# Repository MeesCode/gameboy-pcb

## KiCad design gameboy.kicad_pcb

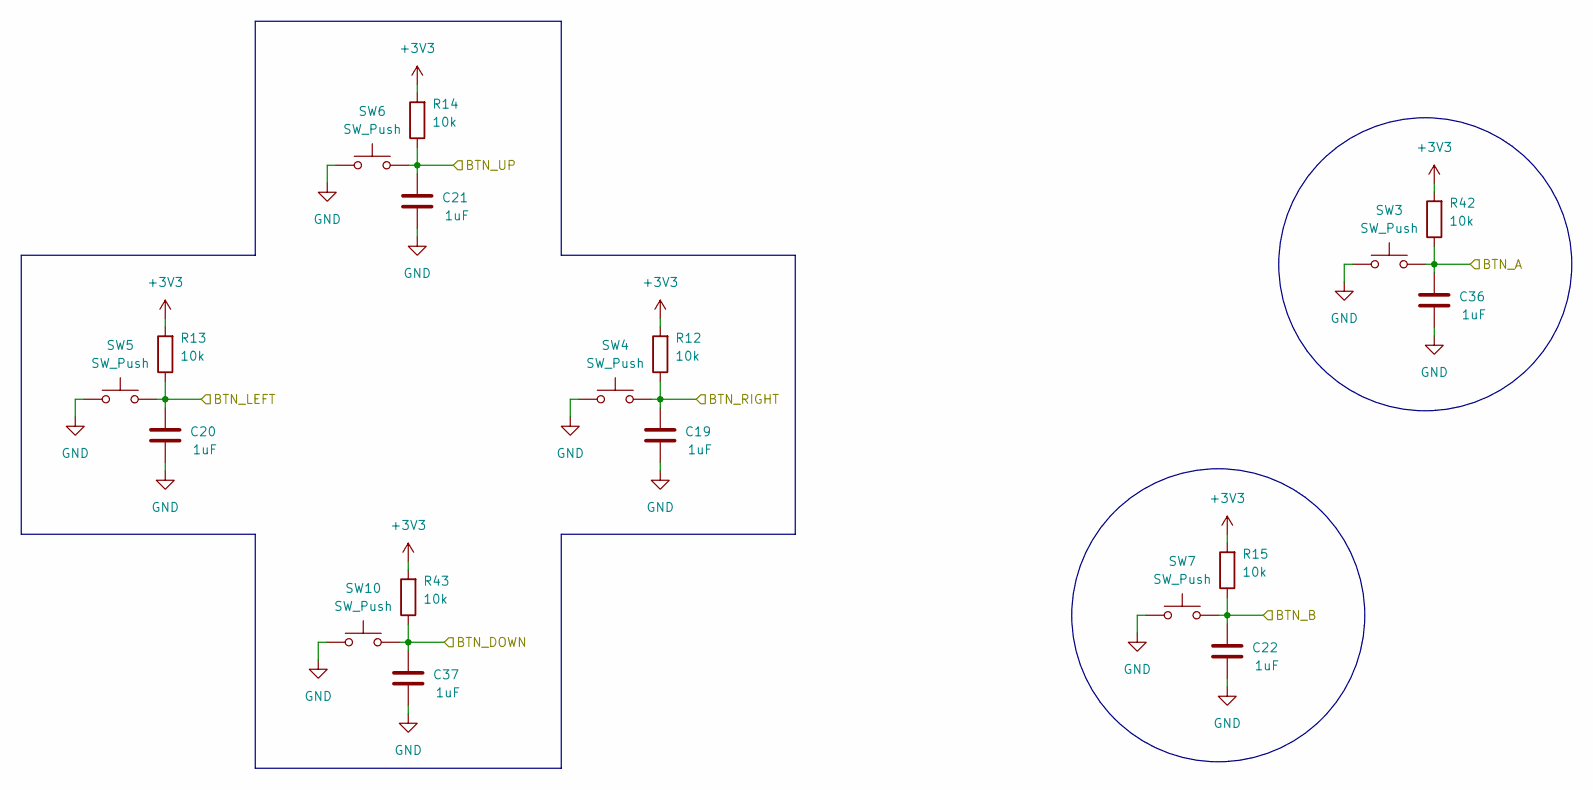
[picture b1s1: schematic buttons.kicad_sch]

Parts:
C19, C20, C21, C22, C36, C37: 1uF; C_0402_1005Metric; Manufacturer Part Number CL05A105KA5NQNC; LCSC C52923
R12, R13, R14, R15, R42, R43: 10k; R_0603_1608Metric
SW3, SW4, SW5, SW6, SW7, SW10: SW_Push; SW_Push_1TS009xxxx-xxxx-xxxx_6x6x5mm; Manufacturer Part Number HX TS665WS 200gf; LCSC C5143657

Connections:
+3V3: R12.2, R13.2, R14.2, R15.2, R42.2, R43.2; also elsewhere on the board
/Buttons/BTN_A: C36.2, R42.1, SW3.2; also elsewhere on the board
/Buttons/BTN_B: C22.2, R15.1, SW7.2; also elsewhere on the board
/Buttons/BTN_DOWN: C37.2, R43.1, SW10.2; also elsewhere on the board
/Buttons/BTN_LEFT: C20.2, R13.1, SW5.2; also elsewhere on the board
/Buttons/BTN_RIGHT: C19.2, R12.1, SW4.2; also elsewhere on the board
/Buttons/BTN_UP: C21.2, R14.1, SW6.2; also elsewhere on the board
GND: C19.1, C20.1, C21.1, C22.1, C36.1, C37.1, SW3.1, SW4.1, SW5.1, SW6.1, SW7.1, SW10.1; also elsewhere on the board

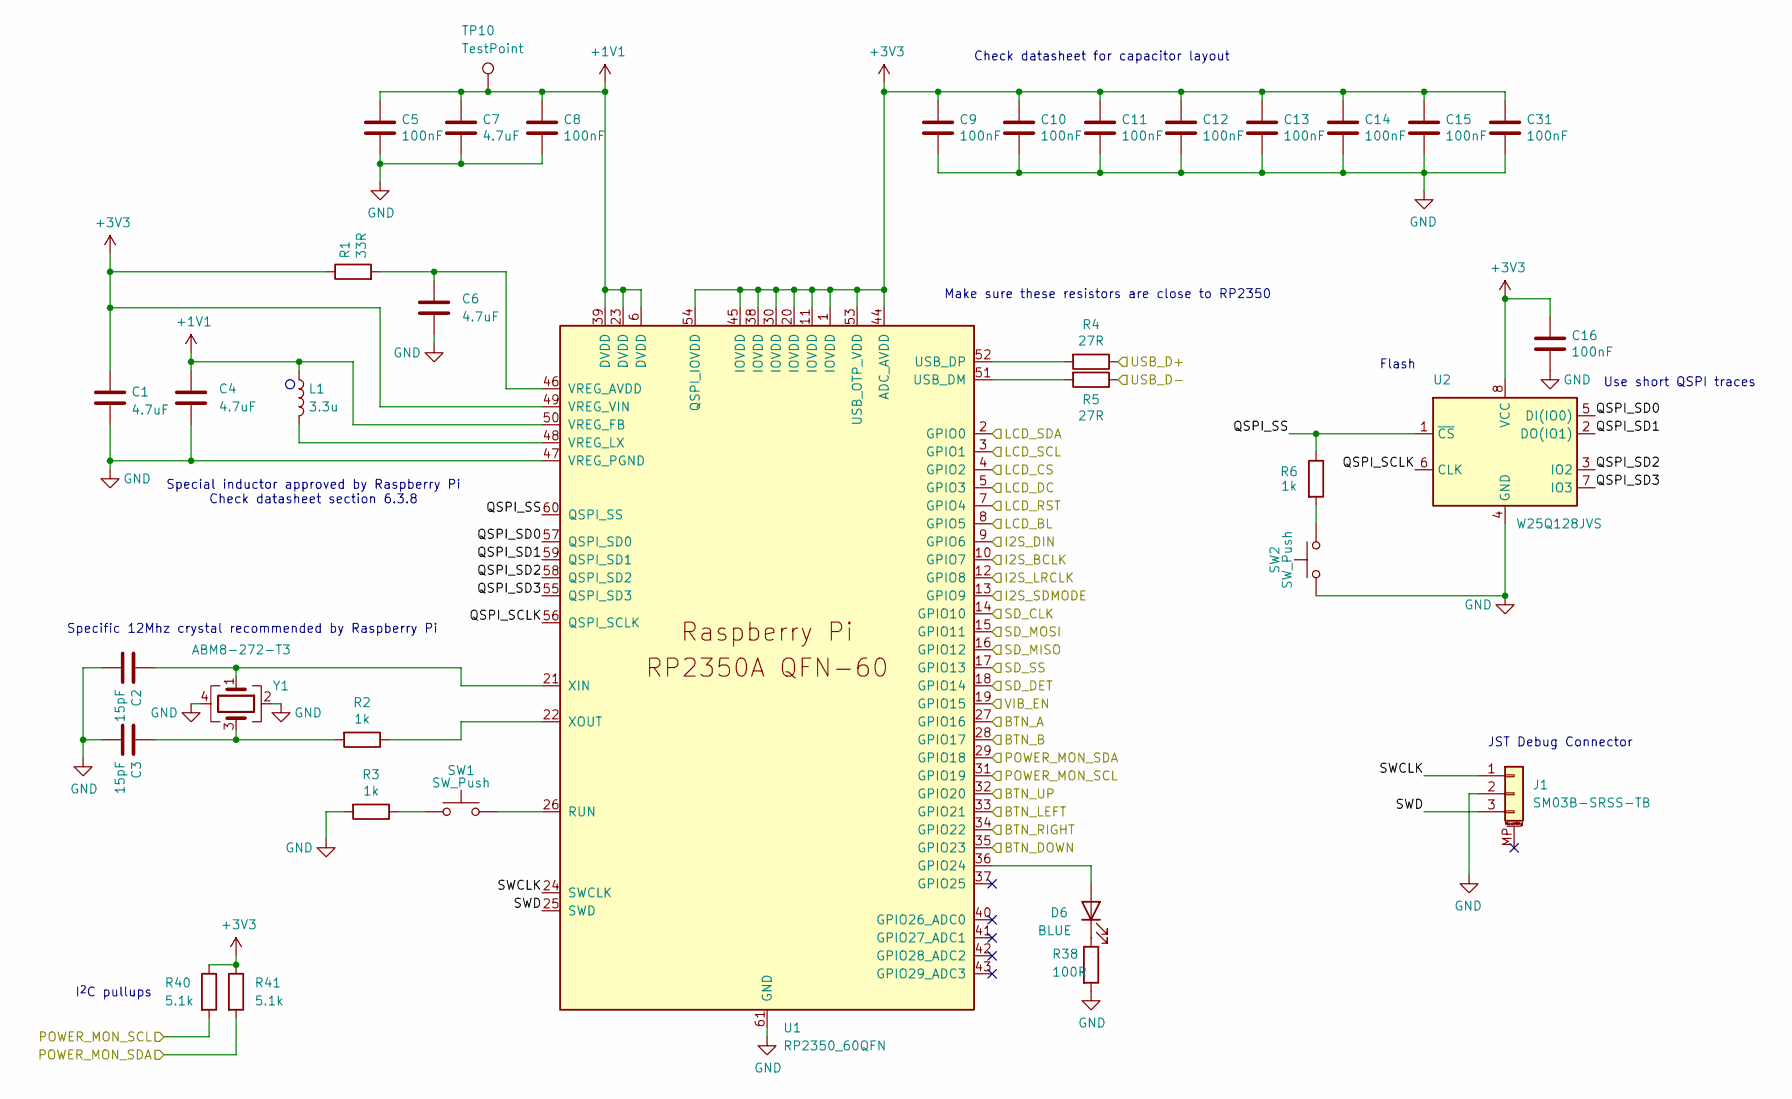
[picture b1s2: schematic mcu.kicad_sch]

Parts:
C1, C4, C6, C7: 4.7uF; C_0402_1005Metric
C2, C3: 15pF; C_0402_1005Metric
C5, C8, C9, C10, C11, C12, C13, C14, C15, C16, C31: 100nF; C_0402_1005Metric
D6: BLUE; LED_Sideways; Manufacturer Part Number XL-1606UBC; LCSC C965865
J1: SM03B-SRSS-TB; JST_SH_SM03B-SRSS-TB_1x03-1MP_P1.00mm_Horizontal; LCSC C160403
L1: 3.3u; L_pol_2016; Manufacturer Part Number AOTA-B201610S3R3-101-T; LCSC C42411119
R1: 33R; R_0402_1005Metric
R2, R3, R6: 1k; R_0603_1608Metric
R4, R5: 27R; R_0402_1005Metric
R38: 100R; R_0603_1608Metric; Manufacturer Part Number 0603WAF1000T5E; LCSC C22775
R40, R41: 5.1k; R_0603_1608Metric
SW1, SW2: SW_Push; SW_Push_1P1T_NO_Vertical_Wuerth_434133025816; Manufacturer Part Number 434133025816; LCSC C843674
TP10: TestPoint; TestPoint_Pad_D1.0mm
U1: RP2350_60QFN; RP2350-QFN-60-1EP_7x7_P0.4mm_EP3.4x3.4mm_ThermalVias; Manufacturer Part Number RP2350A; LCSC C42411118
U2: W25Q128JVS; SOIC-8_5.3x5.3mm_P1.27mm; Manufacturer Part Number W25Q128JVSIQ; LCSC C113767
Y1: ABM8-272-T3; Crystal_SMD_3225-4Pin_3.2x2.5mm; Manufacturer Part Number ABM8-272-T3; LCSC C20625731

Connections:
+1V1: C4.1, C5.1, C7.1, C8.1, L1.1, TP10.1 (1_1), U1.6 (DVDD), U1.23 (DVDD), U1.39 (DVDD), U1.50 (VREG_FB)
+3V3: C1.1, C9.1, C10.1, C11.1, C12.1, C13.1, C14.1, C15.1, C16.1, C31.1, R1.1, R40.1, R41.1, U1.1 (IOVDD), U1.11 (IOVDD), U1.20 (IOVDD), U1.30 (IOVDD), U1.38 (IOVDD), U1.44 (ADC_AVDD), U1.45 (IOVDD), U1.49 (VREG_VIN), U1.53 (USB_OTP_VDD), U1.54 (QSPI_IOVDD), U2.8 (VCC); also elsewhere on the board
/Audio/I2S_BCLK: U1.10 (GPIO7); also elsewhere on the board
/Audio/I2S_DIN: U1.9 (GPIO6); also elsewhere on the board
/Audio/I2S_LRCLK: U1.12 (GPIO8); also elsewhere on the board
/Audio/I2S_SDMODE: U1.13 (GPIO9); also elsewhere on the board
/Buttons/BTN_A: U1.27 (GPIO16); also elsewhere on the board
/Buttons/BTN_B: U1.28 (GPIO17); also elsewhere on the board
/Buttons/BTN_DOWN: U1.35 (GPIO23); also elsewhere on the board
/Buttons/BTN_LEFT: U1.33 (GPIO21); also elsewhere on the board
/Buttons/BTN_RIGHT: U1.34 (GPIO22); also elsewhere on the board
/Buttons/BTN_UP: U1.32 (GPIO20); also elsewhere on the board
/LCD/LCD_BL: U1.8 (GPIO5); also elsewhere on the board
/LCD/LCD_CS: U1.4 (GPIO2); also elsewhere on the board
/LCD/LCD_DC: U1.5 (GPIO3); also elsewhere on the board
/LCD/LCD_RST: U1.7 (GPIO4); also elsewhere on the board
/LCD/LCD_SCL: U1.3 (GPIO1); also elsewhere on the board
/LCD/LCD_SDA: U1.2 (GPIO0); also elsewhere on the board
/MCU/POWER_MON_SCL: R40.2, U1.31 (GPIO19); also elsewhere on the board
/MCU/POWER_MON_SDA: R41.2, U1.29 (GPIO18); also elsewhere on the board
/MCU/QSPI_SCLK: U1.56 (QSPI_SCLK), U2.6 (CLK)
/MCU/QSPI_SD0: U1.57 (QSPI_SD0), U2.5 (DI(IO0))
/MCU/QSPI_SD1: U1.59 (QSPI_SD1), U2.2 (DO(IO1))
/MCU/QSPI_SD2: U1.58 (QSPI_SD2), U2.3 (IO2)
/MCU/QSPI_SD3: U1.55 (QSPI_SD3), U2.7 (IO3)
/MCU/QSPI_SS: R6.1, U1.60 (QSPI_SS), U2.1 (~CS)
/MCU/SD_CLK: U1.14 (GPIO10); also elsewhere on the board
/MCU/SD_DET: U1.18 (GPIO14); also elsewhere on the board
/MCU/SD_MISO: U1.16 (GPIO12); also elsewhere on the board
/MCU/SD_MOSI: U1.15 (GPIO11); also elsewhere on the board
/MCU/SD_SS: U1.17 (GPIO13); also elsewhere on the board
/MCU/SWCLK: J1.1, U1.24 (SWCLK)
/MCU/SWD: J1.3, U1.25 (SWD)
/MCU/USB_D+: R4.1; also elsewhere on the board
/MCU/USB_D-: R5.1; also elsewhere on the board
/MCU/VIB_EN: U1.19 (GPIO15); also elsewhere on the board
GND: C1.2, C2.2, C3.2, C4.2, C5.2, C6.2, C7.2, C8.2, C9.2, C10.2, C11.2, C12.2, C13.2, C14.2, C15.2, C16.2, C31.2, J1.2, R3.2, R38.2, SW2.1, U1.47 (VREG_PGND), U1.61 (GND), U2.4 (GND), Y1.2, Y1.4; also elsewhere on the board
unnamed: C3.1, R2.2, Y1.3
unnamed: D6.2 (A), U1.36 (GPIO24)
unnamed: D6.1 (K), R38.1
unnamed: R3.1, SW1.1
unnamed: R6.2, SW2.2
unnamed: SW1.2, U1.26 (RUN)
unnamed: R5.2, U1.51 (USB_DM)
unnamed: R4.2, U1.52 (USB_DP)
unnamed: C6.1, R1.2, U1.46 (VREG_AVDD)
unnamed: L1.2, U1.48 (VREG_LX)
unnamed: C2.1, U1.21 (XIN), Y1.1
unnamed: R2.1, U1.22 (XOUT)

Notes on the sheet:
Check datasheet for capacitor layout
Special inductor approved by Raspberry Pi Check datasheet section 6.3.8
Specific 12Mhz crystal recommended by Raspberry Pi
Use short QSPI traces
Make sure these resistors are close to RP2350
Flash
I^{2}C pullups
JST Debug Connector

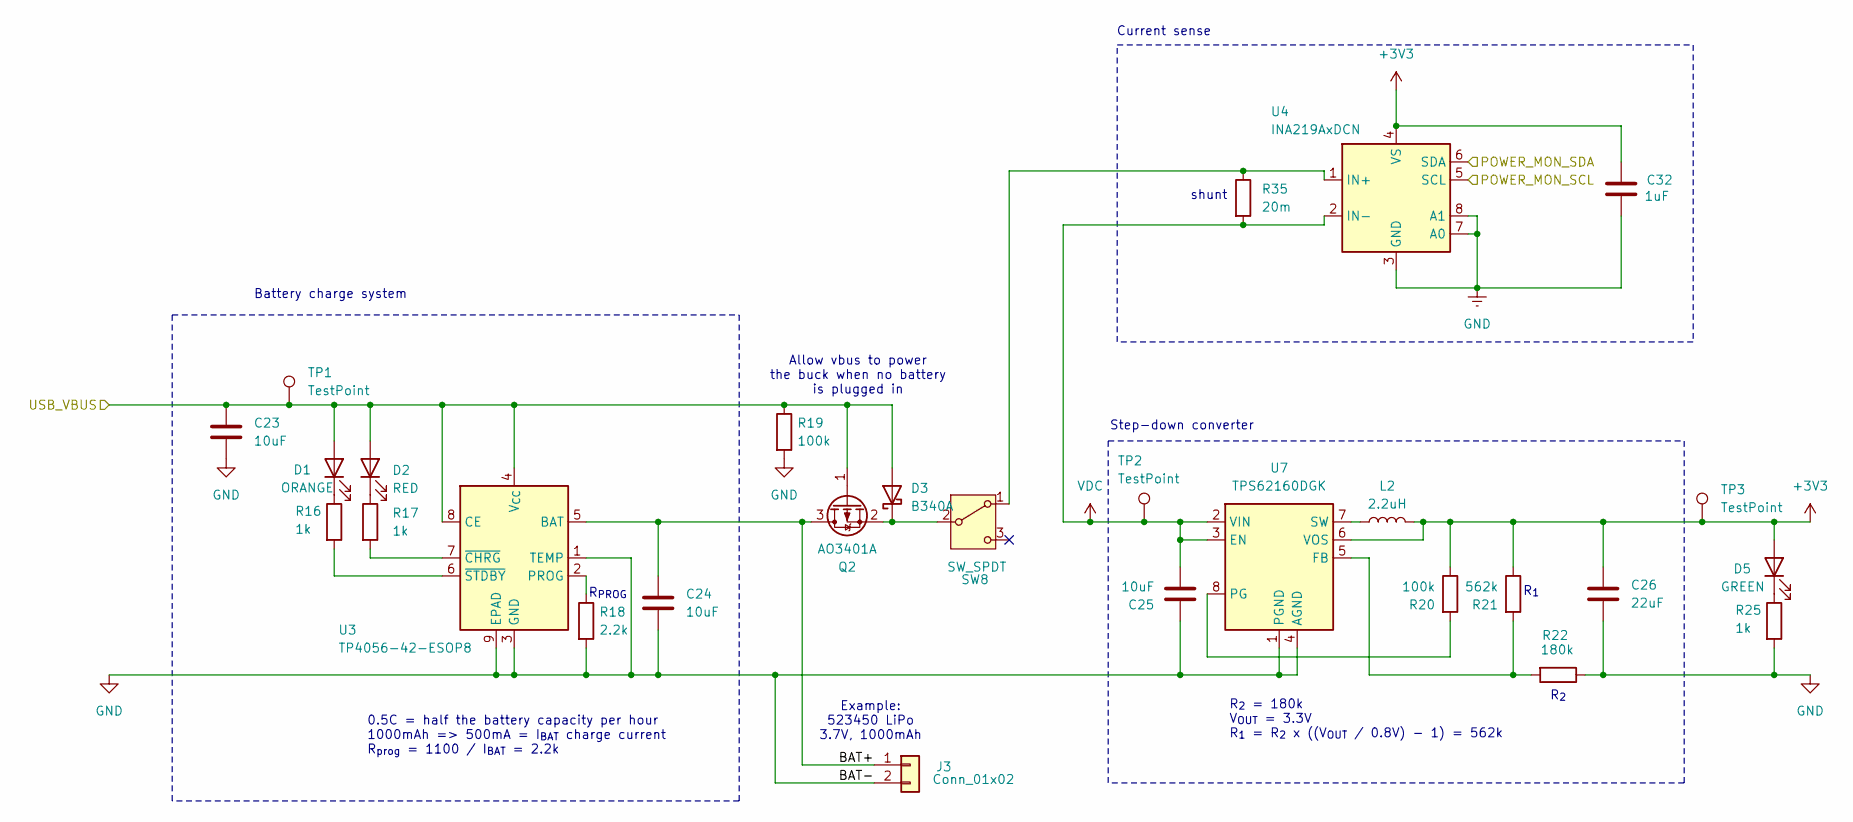
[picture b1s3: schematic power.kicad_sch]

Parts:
C23, C24, C25: 10uF; C_0805_2012Metric
C26: 22uF; C_0603_1608Metric
C32: 1uF; C_0402_1005Metric; Manufacturer Part Number CL05A105KA5NQNC; LCSC C52923
D1: ORANGE; LED_Sideways; Manufacturer Part Number XL-1606UOC; LCSC C965861
D2: RED; LED_Sideways; Manufacturer Part Number XL-1606SURC; LCSC C965860
D3: B340A; D_SMA; Manufacturer Part Number B340A; LCSC C64982
D5: GREEN; LED_Sideways; Manufacturer Part Number XL-1606SYGC; LCSC C965864
J3: Conn_01x02; JST_PH_S2B-PH-SM4-TB_1x02-1MP_P2.00mm_Horizontal; Manufacturer Part Number S2B-PH-SM4-TB(LF)(SN); LCSC C295747
L2: 2.2uH; L_KOHERelec_MDA7030; Manufacturer Part Number APH0630T2R2M; LCSC C5349701
Q2: AO3401A; SOT-23; Manufacturer Part Number AO3401A; LCSC C347476
R16, R17, R25: 1k; R_0603_1608Metric
R18: 2.2k; R_0603_1608Metric
R19, R20: 100k; R_0603_1608Metric
R21: 562k; R_0603_1608Metric
R22: 180k; R_0603_1608Metric
R35: 20m; R_1206_3216Metric; LCSC C393094
SW8: SW_SPDT; SW_SPDT_CK_JS102011SAQN; Manufacturer Part Number JS102011SAQN; LCSC C221660
TP1, TP2, TP3: TestPoint; TestPoint_Pad_D1.0mm
U3: TP4056-42-ESOP8; SOIC-8-1EP_3.9x4.9mm_P1.27mm_EP2.41x3.3mm_ThermalVias; Manufacturer Part Number TP4056-42-ESOP8; LCSC C16581
U4: INA219AxDCN; SOT-23-8; LCSC C87469
U7: TPS62160DGK; MSOP-8_3x3mm_P0.65mm; Manufacturer Part Number TPS62160DGKR; LCSC C60726

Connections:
+3V3: C26.1, C32.2, D5.2 (A), L2.2, R20.1, R21.1, TP3.1 (1_1), U4.4 (VS), U7.6 (VOS); also elsewhere on the board
/MCU/POWER_MON_SCL: U4.5 (SCL); also elsewhere on the board
/MCU/POWER_MON_SDA: U4.6 (SDA); also elsewhere on the board
/Power/BAT+: C24.1, J3.1, Q2.3 (D), U3.5 (BAT)
/Power/USB_VBUS: C23.1, D1.2 (A), D2.2 (A), D3.2 (A), Q2.1 (G), R19.1, TP1.1 (1_1), U3.4 (V_{CC}), U3.8 (CE); also elsewhere on the board
GND: C23.2, C24.2, C25.2, C26.2, C32.1, J3.2, R18.2, R19.2, R22.1, R25.2, U3.1 (TEMP), U3.3 (GND), U3.9 (EPAD), U4.3 (GND), U4.7 (A0), U4.8 (A1), U7.1 (PGND), U7.4 (AGND); also elsewhere on the board
unnamed: D1.1 (K), R16.1
unnamed: D2.1 (K), R17.1
unnamed: D3.1 (K), Q2.2 (S), SW8.2 (B)
unnamed: D5.1 (K), R25.1
unnamed: R35.1, SW8.1 (A), U4.1 (IN+)
unnamed: R18.1, U3.2 (PROG)
unnamed: R17.2, U3.7 (~CHRG)
unnamed: R16.2, U3.6 (~STDBY)
unnamed: R21.2, R22.2, U7.5 (FB)
unnamed: R20.2, U7.8 (PG)
unnamed: L2.1, U7.7 (SW)
VDC: C25.1, R35.2, TP2.1 (1_1), U4.2 (IN-), U7.2 (VIN), U7.3 (EN)

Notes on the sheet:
shunt
Example: 523450 LiPo 3.7V, 1000mAh
R_{1}
Current sense
R_{2} = 180k V_{OUT} = 3.3V R_{1} = R_{2} x ((V_{OUT} / 0.8V) - 1) = 562k
Battery charge system
R_{PROG}
0.5C = half the battery capacity per hour 1000mAh => 500mA = I_{BAT} charge current R_{prog} = 1100 / I_{BAT} = 2.2k
Allow vbus to power the buck when no battery is plugged in
R_{2}
Step-down converter

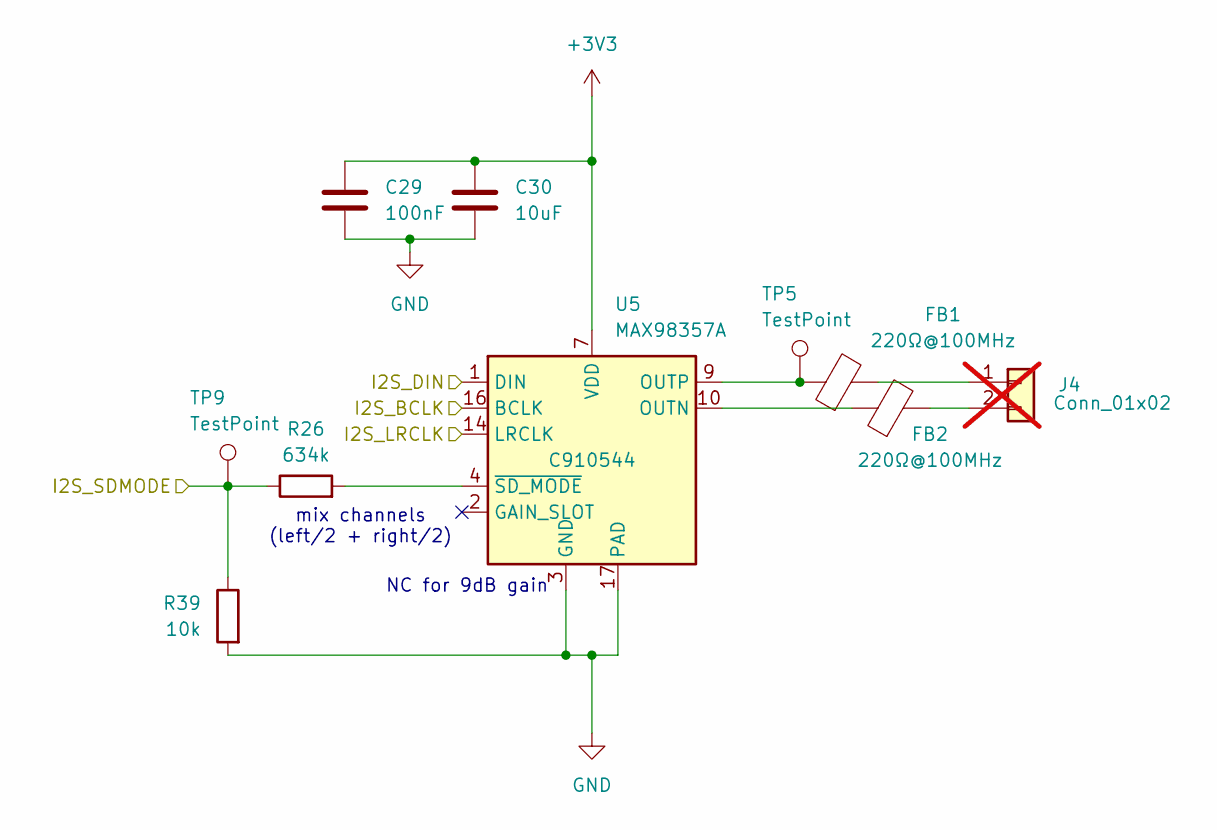
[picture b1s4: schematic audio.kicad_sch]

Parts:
C29: 100nF; C_0603_1608Metric
C30: 10uF; C_0805_2012Metric
FB1, FB2: 220Ω@100MHz; L_0603_1608Metric; Manufacturer Part Number MPZ1608S221ATA00; LCSC C76815
J4: Conn_01x02; JST_PH_S2B-PH-SM4-TB_1x02-1MP_P2.00mm_Horizontal; Manufacturer Part Number S2B-PH-SM4-TB(LF)(SN); LCSC C295747; not fitted
R26: 634k; R_0603_1608Metric; LCSC C2999499
R39: 10k; R_0603_1608Metric
TP5, TP9: TestPoint; TestPoint_Pad_D1.0mm
U5: MAX98357A; TQFN-16-1EP_3x3mm_P0.5mm_EP1.23x1.23mm; LCSC C910544

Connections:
+3V3: C29.1, C30.1, U5.7 (VDD), U5.8 (VDD); also elsewhere on the board
/Audio/I2S_BCLK: U5.16 (BCLK); also elsewhere on the board
/Audio/I2S_DIN: U5.1 (DIN); also elsewhere on the board
/Audio/I2S_LRCLK: U5.14 (LRCLK); also elsewhere on the board
/Audio/I2S_SDMODE: R26.1, R39.1, TP9.1 (1_1); also elsewhere on the board
GND: C29.2, C30.2, R39.2, U5.3 (GND), U5.11 (GND), U5.15 (GND), U5.17 (PAD); also elsewhere on the board
unnamed: FB1.2, J4.1
unnamed: FB2.2, J4.2
unnamed: FB2.1, U5.10 (OUTN)
unnamed: FB1.1, TP5.1 (1_1), U5.9 (OUTP)
unnamed: R26.2, U5.4 (~SD_MODE)

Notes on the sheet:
mix channels (left/2 + right/2)
NC for 9dB gain

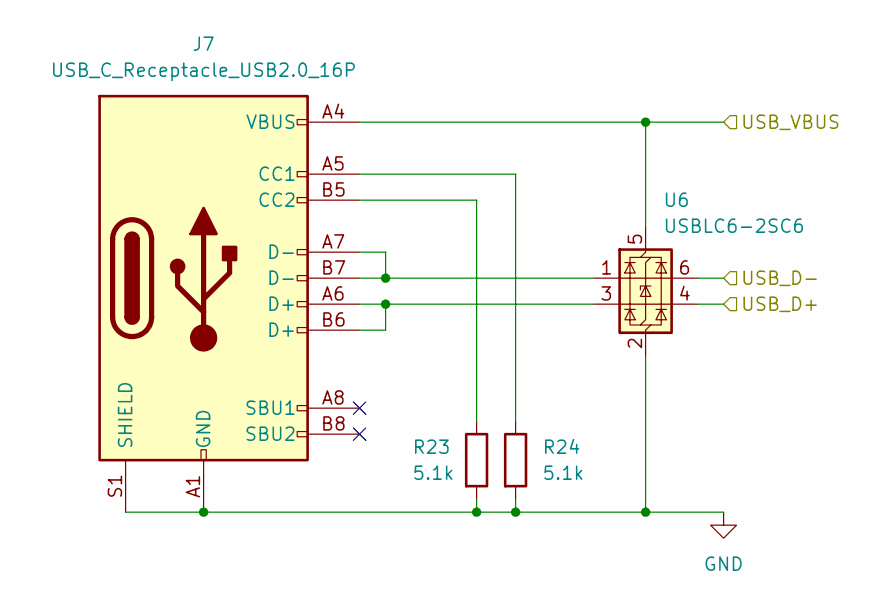
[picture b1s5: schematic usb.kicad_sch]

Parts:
J7: USB_C_Receptacle_USB2.0_16P; USB_C_Receptacle_GCT_USB4105-xx-A_16P_TopMnt_Horizontal; Manufacturer Part Number TYPE-C 16PIN 2MD(073); LCSC C2765186
R23, R24: 5.1k; R_0603_1608Metric
U6: USBLC6-2SC6; SOT-23-6; Manufacturer Part Number USBLC6-2SC6; LCSC C2827654

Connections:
/MCU/USB_D+: U6.4 (I/O2); also elsewhere on the board
/MCU/USB_D-: U6.6 (I/O1); also elsewhere on the board
/Power/USB_VBUS: J7.A4 (VBUS), J7.A9 (VBUS), J7.B4 (VBUS), J7.B9 (VBUS), U6.5 (VBUS); also elsewhere on the board
GND: J7.A1 (GND), J7.A12 (GND), J7.B1 (GND), J7.B12 (GND), J7.S1 (SHIELD), R23.2, R24.2, U6.2 (GND); also elsewhere on the board
unnamed: J7.A5 (CC1), R24.1
unnamed: J7.B5 (CC2), R23.1
unnamed: J7.A6 (D+), J7.B6 (D+), U6.3 (I/O2)
unnamed: J7.A7 (D-), J7.B7 (D-), U6.1 (I/O1)

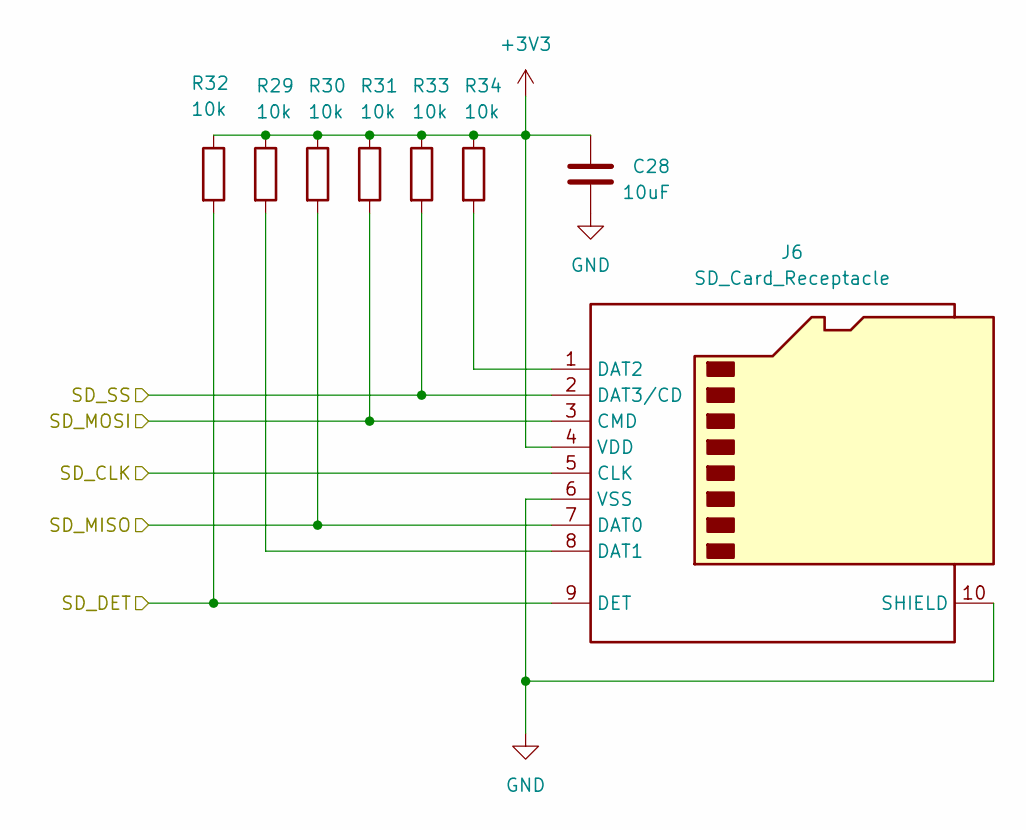
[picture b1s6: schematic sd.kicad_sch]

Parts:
C28: 10uF; C_0805_2012Metric
J6: SD_Card_Receptacle; SHOU HAN; Manufacturer Part Number TF PUSH; LCSC C393941
R29, R30, R31, R32, R33, R34: 10k; R_0603_1608Metric

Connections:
+3V3: C28.1, J6.4 (VDD), R29.1, R30.1, R31.1, R32.1, R33.1, R34.1; also elsewhere on the board
/MCU/SD_CLK: J6.5 (CLK); also elsewhere on the board
/MCU/SD_DET: J6.9 (DET), R32.2; also elsewhere on the board
/MCU/SD_MISO: J6.7 (DAT0), R30.2; also elsewhere on the board
/MCU/SD_MOSI: J6.3 (CMD), R31.2; also elsewhere on the board
/MCU/SD_SS: J6.2 (DAT3/CD), R33.2; also elsewhere on the board
GND: C28.2, J6.6 (VSS), J6.10 (SHIELD); also elsewhere on the board
unnamed: J6.8 (DAT1), R29.2
unnamed: J6.1 (DAT2), R34.2

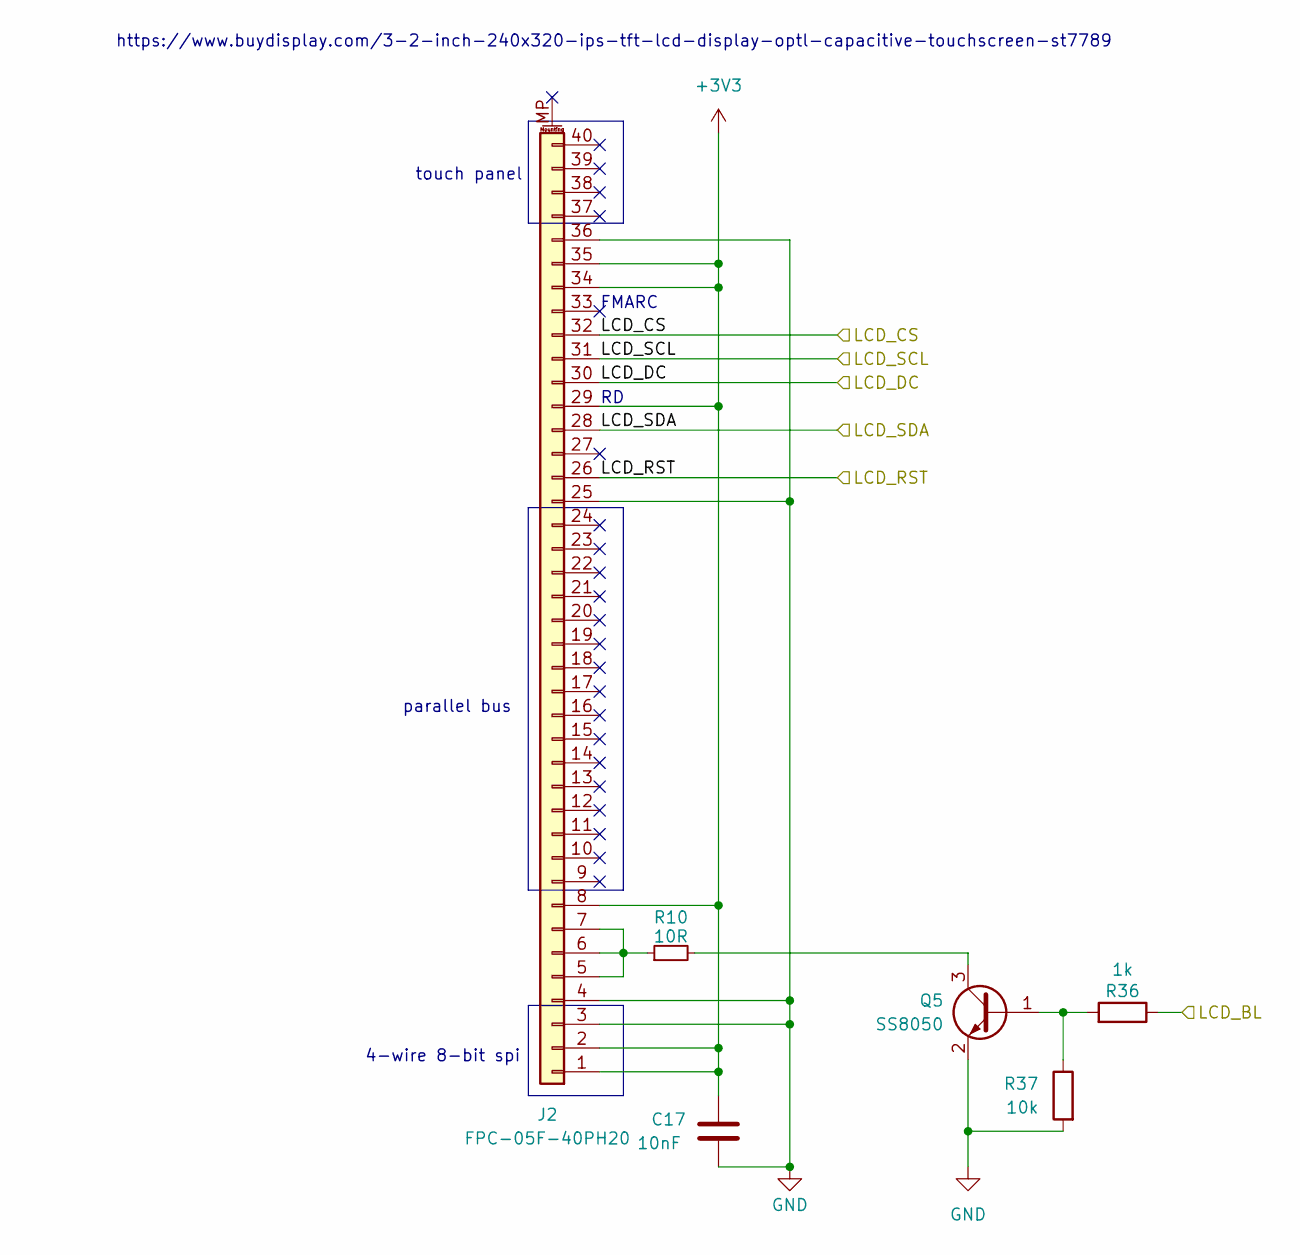
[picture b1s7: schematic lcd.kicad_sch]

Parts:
C17: 10nF; C_0402_1005Metric
J2: FPC-05F-40PH20; TE_4-1734839-0_1x40-1MP_P0.5mm_Horizontal; Manufacturer Part Number AFC07-S40ECA-00; LCSC C262648
Q5: SS8050; SOT-23; Manufacturer Part Number SS8050; LCSC C916392
R10: 10R; R_0603_1608Metric
R36: 1k; R_0603_1608Metric
R37: 10k; R_0603_1608Metric

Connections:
+3V3: C17.2, J2.1, J2.2, J2.8, J2.29, J2.34, J2.35; also elsewhere on the board
/LCD/LCD_BL: R36.1; also elsewhere on the board
/LCD/LCD_CS: J2.32; also elsewhere on the board
/LCD/LCD_DC: J2.30; also elsewhere on the board
/LCD/LCD_RST: J2.26; also elsewhere on the board
/LCD/LCD_SCL: J2.31; also elsewhere on the board
/LCD/LCD_SDA: J2.28; also elsewhere on the board
GND: C17.1, J2.3, J2.4, J2.25, J2.36, Q5.2 (E), R37.2; also elsewhere on the board
unnamed: J2.5, J2.6, J2.7, R10.1
unnamed: Q5.1 (B), R36.2, R37.1
unnamed: Q5.3 (C), R10.2

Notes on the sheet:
https://www.buydisplay.com/3-2-inch-240x320-ips-tft-lcd-display-optl-capacitive-touchscreen-st7789
parallel bus
FMARC
4-wire 8-bit spi
touch panel

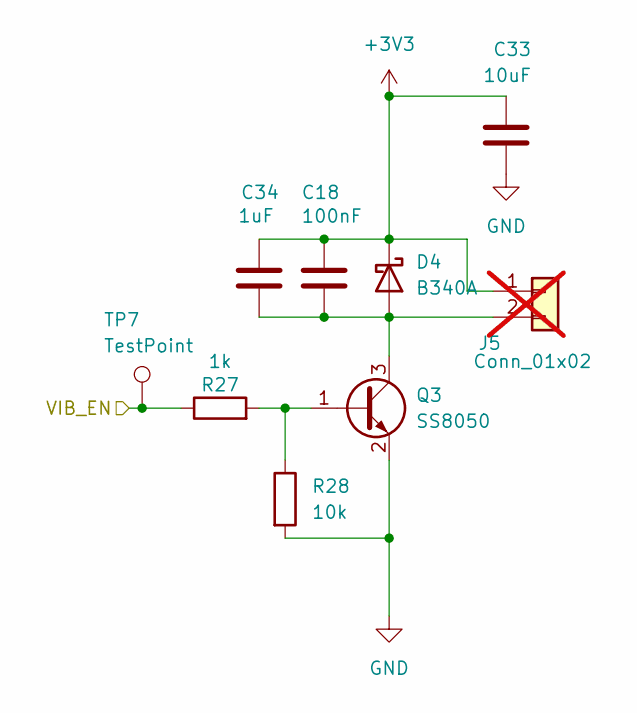
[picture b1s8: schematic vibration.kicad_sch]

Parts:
C18: 100nF; C_0402_1005Metric
C33: 10uF; C_0805_2012Metric
C34: 1uF; C_0402_1005Metric; Manufacturer Part Number CL05A105KA5NQNC; LCSC C52923
D4: B340A; D_SMA; Manufacturer Part Number B340A; LCSC C64982
J5: Conn_01x02; JST_PH_S2B-PH-SM4-TB_1x02-1MP_P2.00mm_Horizontal; Manufacturer Part Number S2B-PH-SM4-TB(LF)(SN); LCSC C295747; not fitted
Q3: SS8050; SOT-23; Manufacturer Part Number SS8050; LCSC C916392
R27: 1k; R_0603_1608Metric
R28: 10k; R_0603_1608Metric
TP7: TestPoint; TestPoint_Pad_D1.0mm

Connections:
+3V3: C18.1, C33.1, C34.2, D4.1 (K), J5.1; also elsewhere on the board
/MCU/VIB_EN: R27.1, TP7.1 (1_1); also elsewhere on the board
GND: C33.2, Q3.2 (E), R28.2; also elsewhere on the board
unnamed: C18.2, C34.1, D4.2 (A), J5.2, Q3.3 (C)
unnamed: Q3.1 (B), R27.2, R28.1

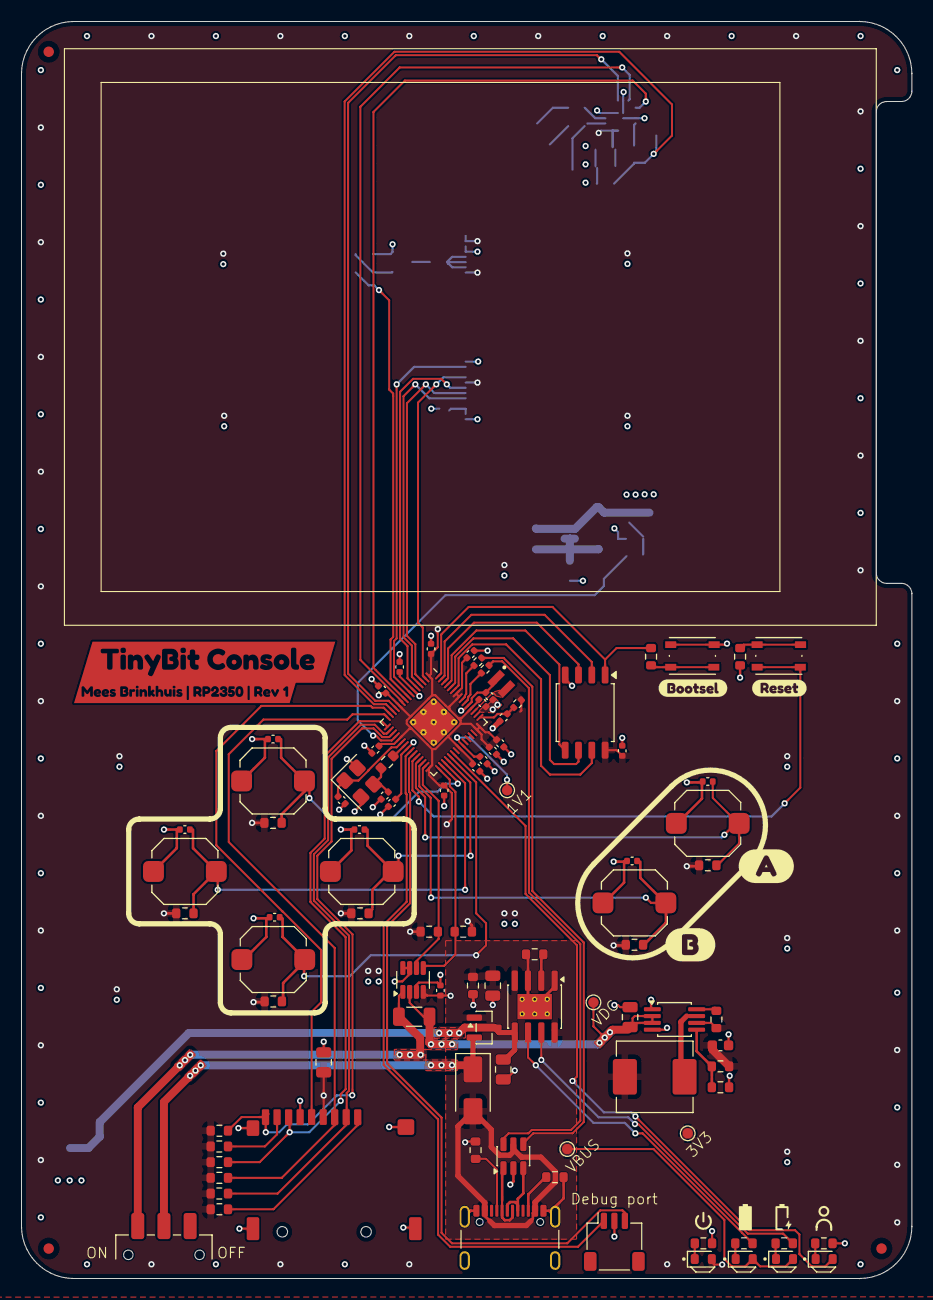
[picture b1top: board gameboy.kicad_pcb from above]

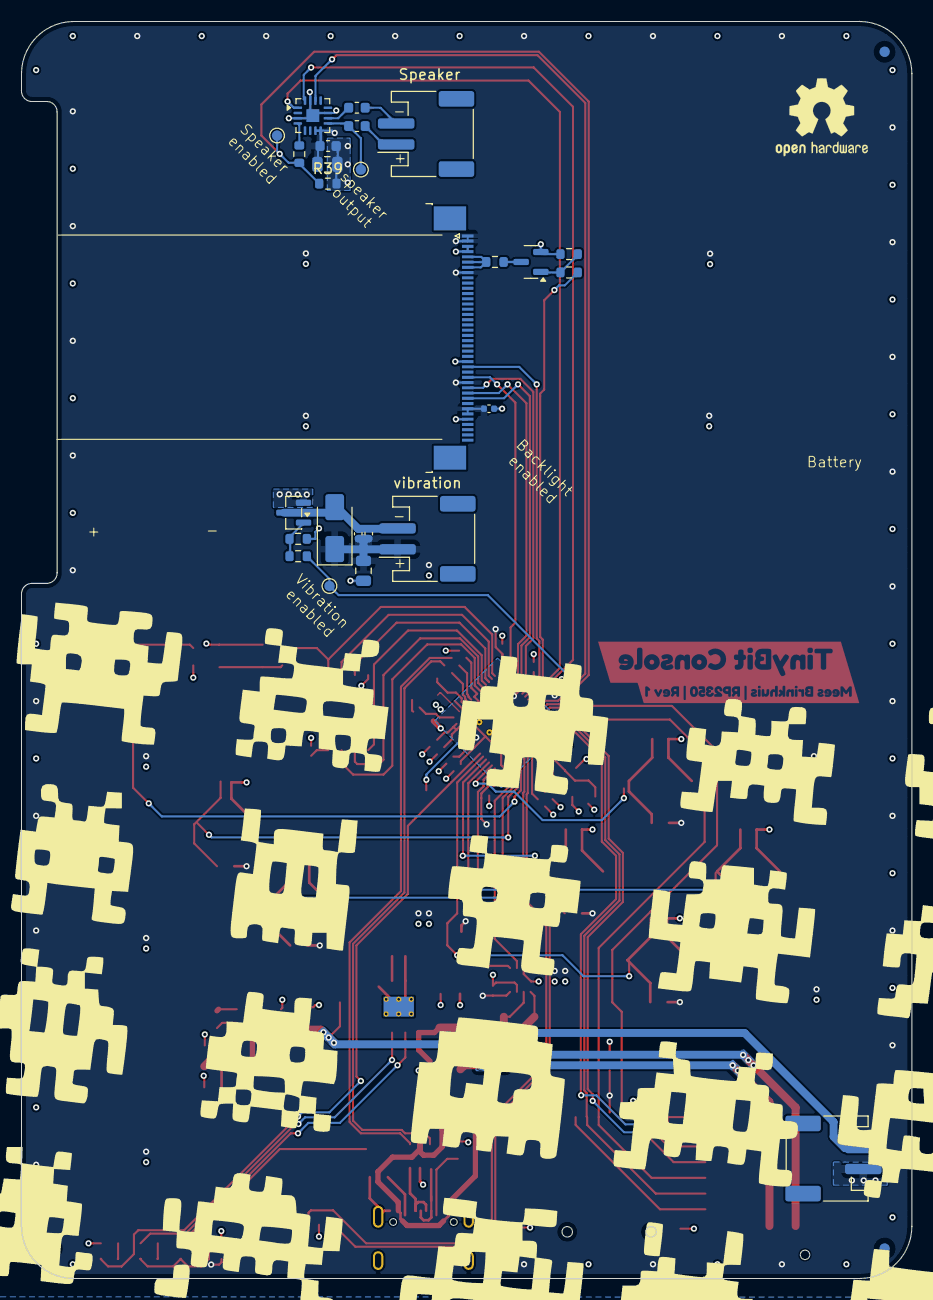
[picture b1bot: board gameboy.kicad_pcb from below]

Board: 4 copper layers, 85.0 x 120.0 mm, 124 parts (26 on the bottom side), 79 nets.

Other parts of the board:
kibuzzard-6ABF64DD: G***; kibuzzard-6ABF64DD
kibuzzard-6ABF6516: G***; kibuzzard-6ABF6516
kibuzzard-6975FF76: G***; kibuzzard-6975FF76
kibuzzard-6973473F: G***; kibuzzard-6973473F
kibuzzard-69734758: G***; kibuzzard-69734758
kibuzzard-69734789: G***; kibuzzard-69734789

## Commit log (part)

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2025-11-30 start with power management
2025-11-30 finish power management
2025-11-30 led driver backlight, not finished
2025-12-01 add buttons and connect lcd
2025-12-01 button debouncing and VDD decoupling
2026-01-09 remove backups, removed old chip
2026-01-10 add rp2350 mcu
2026-01-10 add usb c connector
2026-01-11 schematic functional and includes current test setup
2026-01-11 add audio amp
2026-01-12 add amplifier mode selector, add drawing lcd
2026-01-12 add on/off switch
2026-01-12 add vibration motor
2026-01-12 add SD card
2026-01-12 small updates in component selection
2026-01-13 check with hardware manual, add comments, add mpns
2026-01-13 cleanup
2026-01-14 fix usb and add esd diodes, some other checks
2026-01-14 whole bunch of layout done
2026-01-18 mcu layout
2026-01-19 place mcu on board
2026-01-19 add partial power system
2026-01-19 more routing
2026-01-20 route vibration and speaker
2026-01-21 overhaul mcu layout, add last components, stitching vias, run DRC
2026-01-21 hide refs
2026-01-21 last bit of cleanup
2026-01-21 change trace cutting zone
2026-01-21 add lcd model
2026-01-21 minor cleanup
2026-01-23 add silkscreen, optimize layout and replace sd card peripheral
2026-01-23 add invaders
2026-01-24 change color lcd model, add more teardrops
2026-01-25 changed size and connectors on the back
2026-01-25 add power monitoring
2026-01-27 proper lcd backlight driver
2026-01-28 extra capacitance vibration, old backlight method
2026-01-30 some small cleanup thingies
2026-02-01 changes for production
2026-02-01 remove redundant passive lcsc numbers
2026-02-03 fix bom
2026-02-03 align some components with inventory
2026-02-03 use one lower mlq component
2026-02-03 silkscreen
2026-02-03 remove references
2026-02-17 changes after testing the display
2026-02-18 add fiducials and mounting holes
2026-02-18 move capacitor lcd
2026-05-10 battery polarity and position
2026-05-10 fix lcd connector orientation
2026-05-10 fix on/off switch routing
2026-05-10 text positioning
